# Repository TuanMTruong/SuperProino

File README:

/****************************************/
/*
 * Author: Tuan Truong
 * This project uses a SuperPro board to
 * communicate with an Arduino board.
 * Since the SuperPro board doesn't have 
 * accessible serial protocol we will be 
 * using an Arduino to create a paraell
 * protocol
 */
/****************************************/

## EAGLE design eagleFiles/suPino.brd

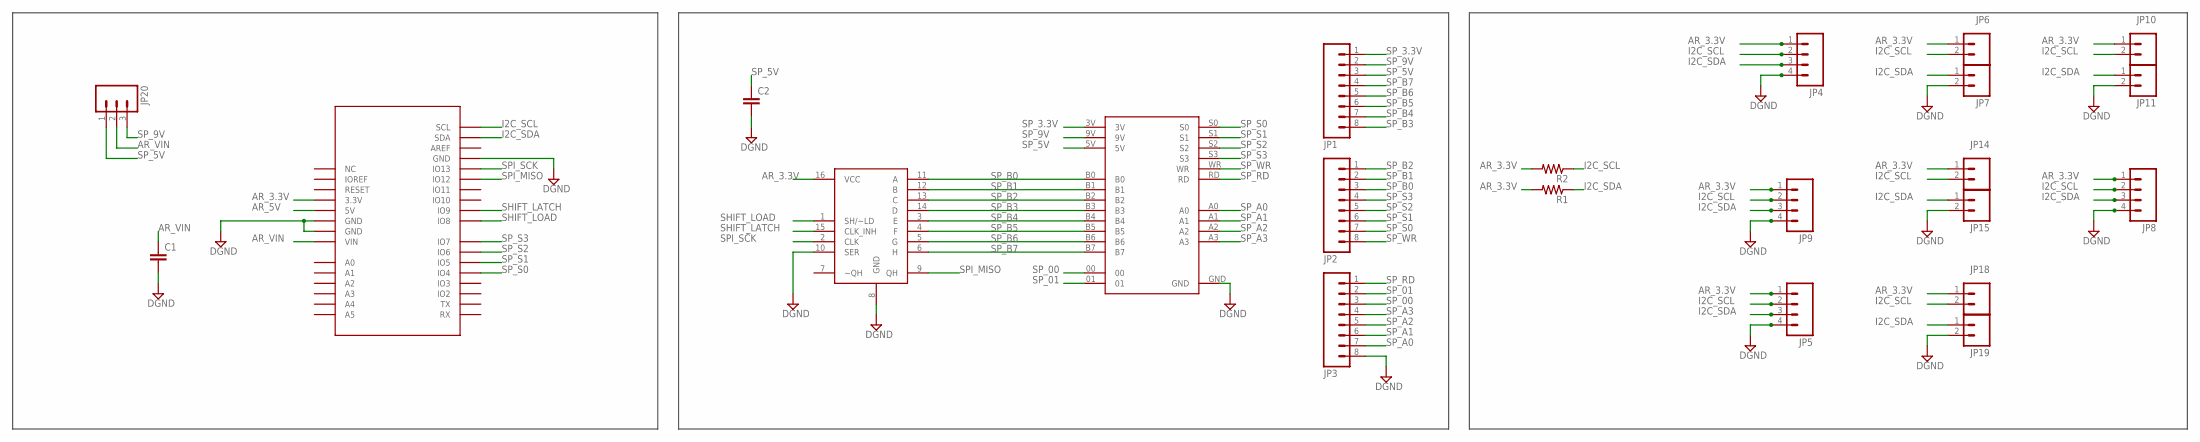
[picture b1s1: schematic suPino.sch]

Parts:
C1, C2: CAP0805; 0805
JP1, JP2, JP3: M08; 1X08_ROUND
JP4, JP5, JP8, JP9: M04PTH; 1X04
JP6, JP7, JP10, JP11, JP14, JP15, JP18, JP19: M023.5MM; SCREWTERMINAL-3.5MM-2
JP20: M03PTH; 1X03
R1, R2: RESISTOR0805-RES; 0805
U$1: ARDUIN_SHIELD; ARDUNIO_SHIELD
U$2: SUPERPRO_BOARD
U$4: 8B_SHIFT_REG; TSSOP16

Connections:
AR_3.3V: JP4.1, JP5.1, JP6.1, JP8.1, JP9.1, JP10.1, JP14.1, JP18.1, R1.2, R2.2, U$1.3.3V, U$4.16 (VCC)
AR_5V: U$1.5V
AR_VIN: C1.1, JP20.2, U$1.VIN
DGND: C1.2, C2.2, JP3.8, JP4.4, JP5.4, JP7.2, JP8.4, JP9.4, JP11.2, JP15.2, JP19.2, U$1.GND@0 (GND), U$1.GND@1 (GND), U$1.GND@2 (GND), U$2.GND, U$4.8 (GND), U$4.10 (SER)
I2C_SCL: JP4.2, JP5.2, JP6.2, JP8.2, JP9.2, JP10.2, JP14.2, JP18.2, R2.1, U$1.SCL
I2C_SDA: JP4.3, JP5.3, JP7.1, JP8.3, JP9.3, JP11.1, JP15.1, JP19.1, R1.1, U$1.SDA
SHIFT_LATCH: U$1.IO9, U$4.15 (CLK_INH)
SHIFT_LOAD: U$1.IO8, U$4.1 (SH/~LD)
SPI_MISO: U$1.IO12, U$4.9 (QH)
SPI_SCK: U$1.IO13, U$4.2 (CLK)
SP_00: JP3.3, U$2.00
SP_01: JP3.2, U$2.01
SP_3.3V: JP1.1, U$2.3V
SP_5V: C2.1, JP1.3, JP20.1, U$2.5V
SP_9V: JP1.2, JP20.3, U$2.9V
SP_A0: JP3.7, U$2.A0
SP_A1: JP3.6, U$2.A1
SP_A2: JP3.5, U$2.A2
SP_A3: JP3.4, U$2.A3
SP_B0: JP2.3, U$2.B0, U$4.11 (A)
SP_B1: JP2.2, U$2.B1, U$4.12 (B)
SP_B2: JP2.1, U$2.B2, U$4.13 (C)
SP_B3: JP1.8, U$2.B3, U$4.14 (D)
SP_B4: JP1.7, U$2.B4, U$4.3 (E)
SP_B5: JP1.6, U$2.B5, U$4.4 (F)
SP_B6: JP1.5, U$2.B6, U$4.5 (G)
SP_B7: JP1.4, U$2.B7, U$4.6 (H)
SP_RD: JP3.1, U$2.RD
SP_S0: JP2.7, U$1.IO4, U$2.S0
SP_S1: JP2.6, U$1.IO5, U$2.S1
SP_S2: JP2.5, U$1.IO6, U$2.S2
SP_S3: JP2.4, U$1.IO7, U$2.S3
SP_WR: JP2.8, U$2.WR

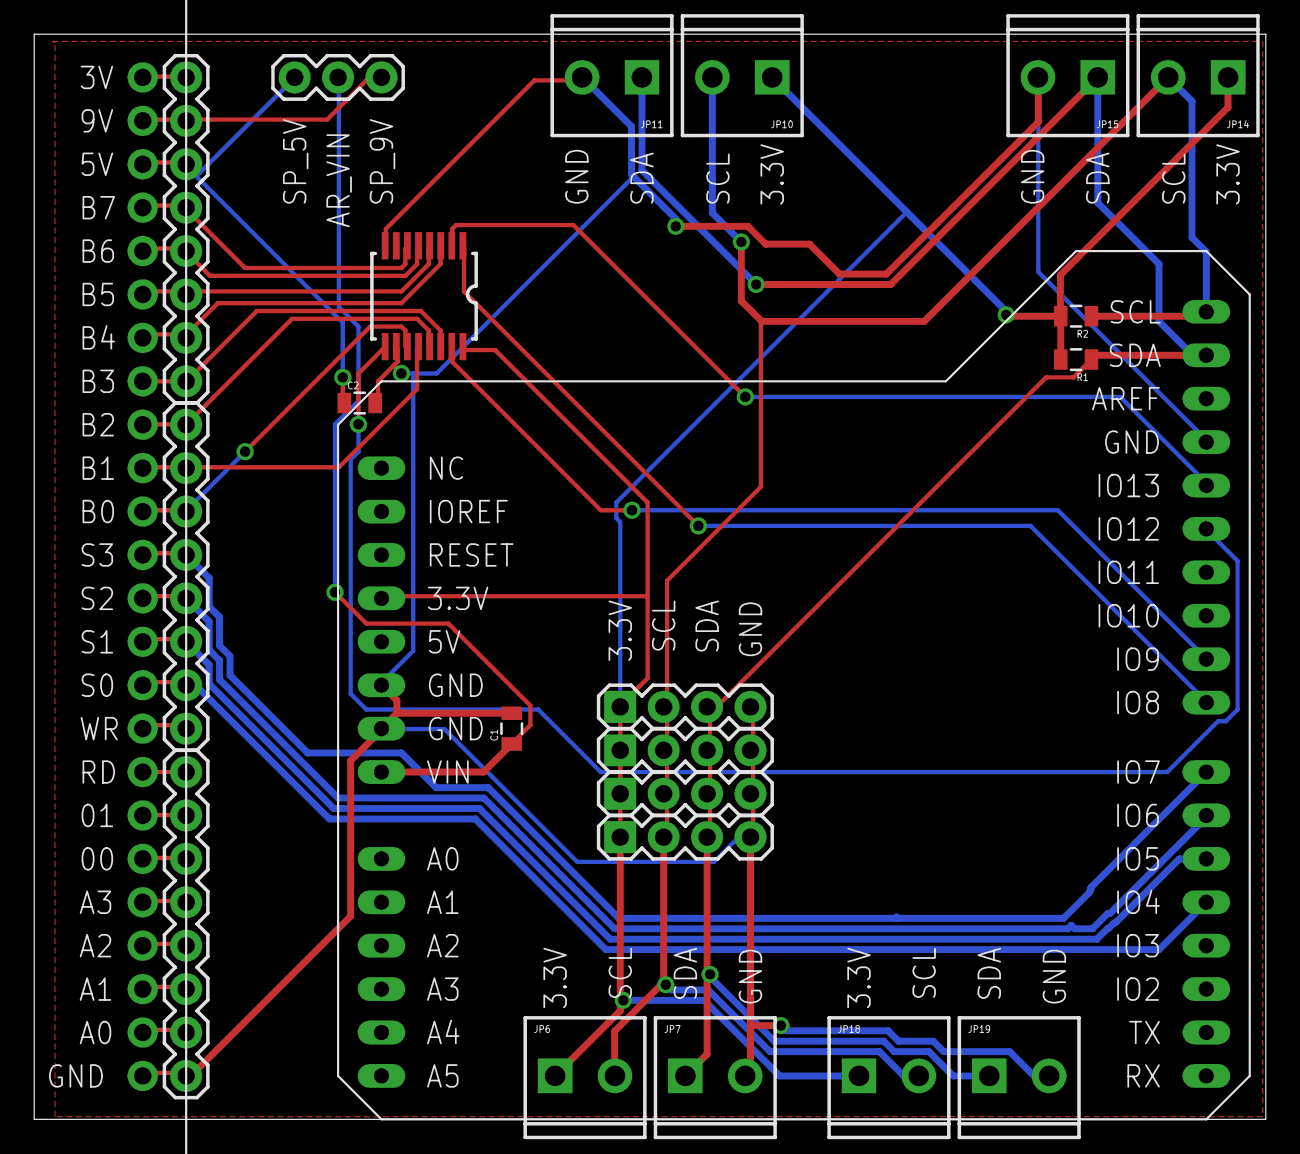
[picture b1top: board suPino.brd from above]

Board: 2 copper layers, 72.1 x 63.5 mm, 23 parts (0 on the bottom side), 32 nets.

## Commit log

2015-02-22 Adding eagle files
2015-02-22 Updated board file still need to add silkscreen lables
2015-02-23 Added test code that use Arduino to talk to sonars Send data to superpro via paraell
2015-03-05 Fixed the routing and added silkscreen
2015-03-05 Creating documentation
2015-03-05 create title
    Need to add picture

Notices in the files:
parts and their libraries:
SparkFun-Capacitors: Licensing: Creative Commons ShareAlike 4.0 International - https://creativecommons.org/licenses/by-sa/4.0
